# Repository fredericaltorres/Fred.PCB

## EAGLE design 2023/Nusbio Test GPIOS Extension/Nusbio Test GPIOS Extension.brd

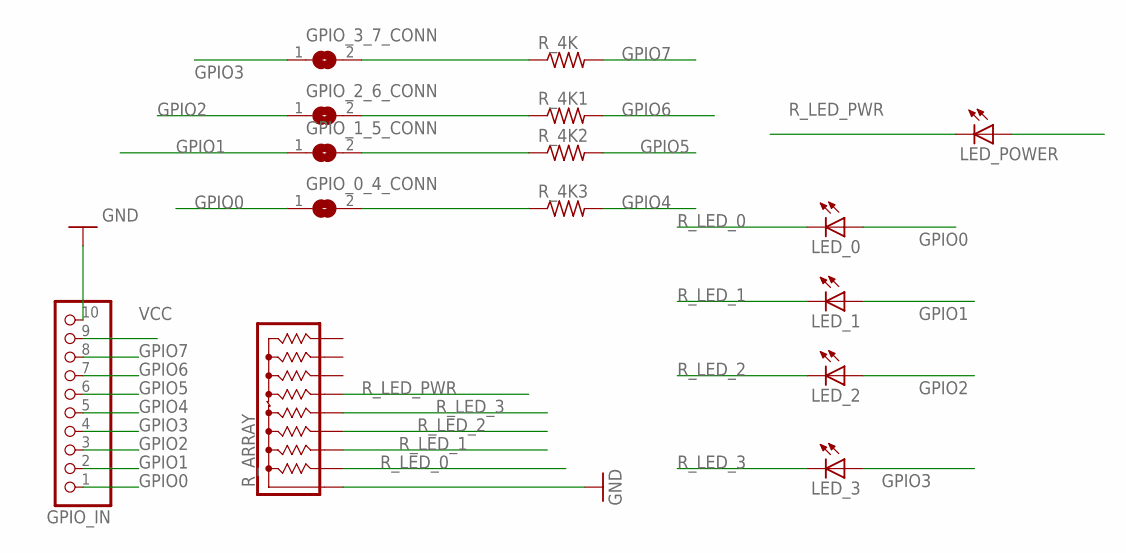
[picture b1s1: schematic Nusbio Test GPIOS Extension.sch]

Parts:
GPIO_0_4_CONN, GPIO_1_5_CONN, GPIO_2_6_CONN, GPIO_3_7_CONN: SOLDERJUMPERREFLOW; SOLDERJUMPER_REFLOW
GPIO_IN: PINHD-1X10; 1X10-BIG
LED_0, LED_1, LED_2, LED_3: LEDSMT1206; 1206
LED_POWER: LEDSMT1206; 1206
R_4K, R_4K1, R_4K2, R_4K3: R-US_R1206; R1206
R_ARRAY: 4609X; SIP9

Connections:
GND: GPIO_IN.10, R_ARRAY.1
GPIO0: GPIO_0_4_CONN.1, GPIO_IN.1, LED_0.A
GPIO1: GPIO_1_5_CONN.1, GPIO_IN.2, LED_1.A
GPIO2: GPIO_2_6_CONN.1, GPIO_IN.3, LED_2.A
GPIO3: GPIO_3_7_CONN.1, GPIO_IN.4, LED_3.A
GPIO4: GPIO_IN.5, R_4K3.2
GPIO5: GPIO_IN.6, R_4K2.2
GPIO6: GPIO_IN.7, R_4K1.2
GPIO7: GPIO_IN.8, R_4K.2; also elsewhere on the board
unnamed 9: GPIO_3_7_CONN.2, R_4K.1; also elsewhere on the board
unnamed: GPIO_2_6_CONN.2, R_4K1.1
unnamed: GPIO_1_5_CONN.2, R_4K2.1
unnamed: GPIO_0_4_CONN.2, R_4K3.1
R_LED_0: LED_0.C, R_ARRAY.2
R_LED_1: LED_1.C, R_ARRAY.3
R_LED_2: LED_2.C, R_ARRAY.4
R_LED_3: LED_3.C, R_ARRAY.5
R_LED_PWR: LED_POWER.C, R_ARRAY.6
VCC: GPIO_IN.9, LED_POWER.A

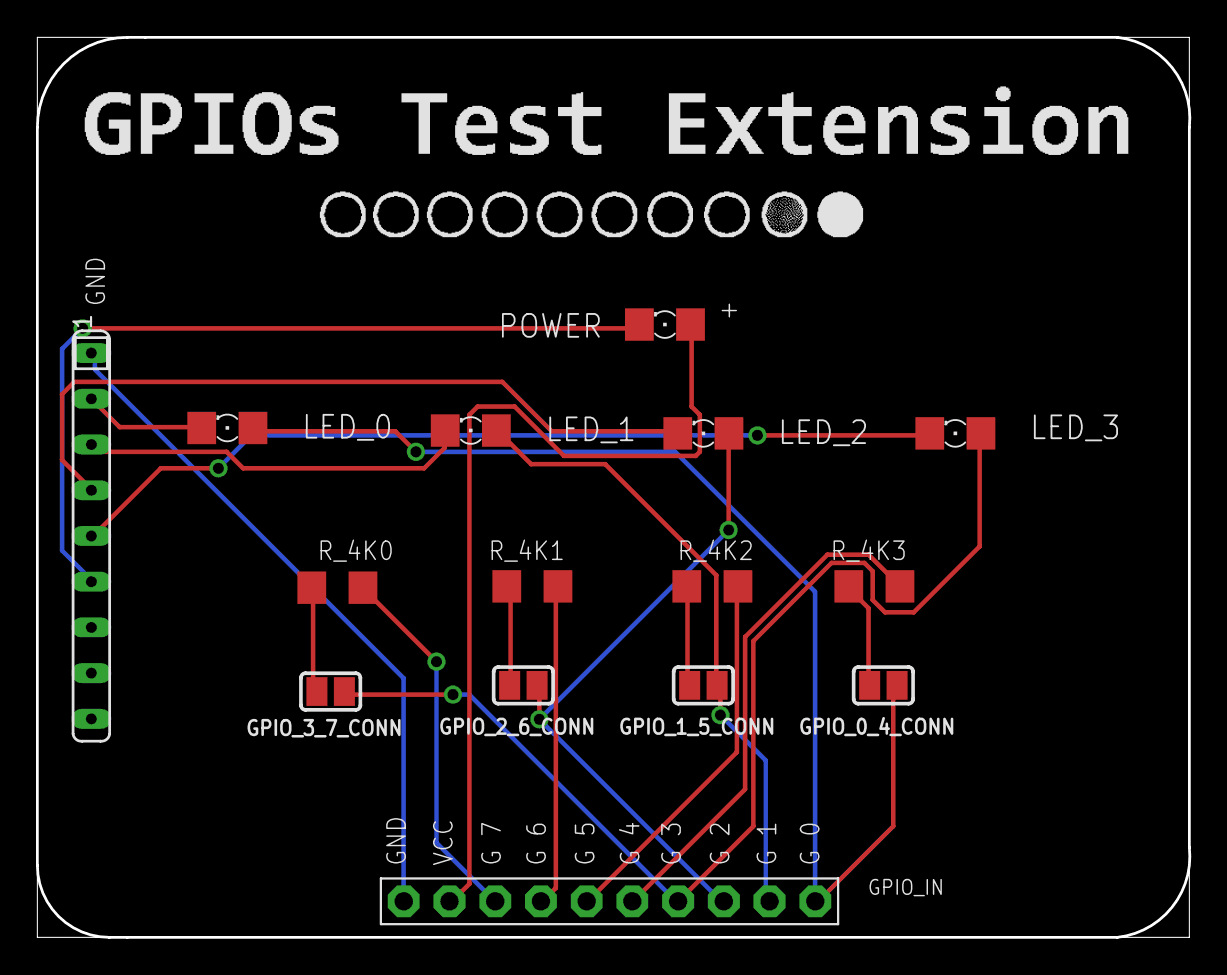
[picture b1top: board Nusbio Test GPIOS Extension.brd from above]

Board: 2 copper layers, 64.0 x 50.0 mm, 15 parts (0 on the bottom side), 19 nets.

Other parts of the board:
R_4K0: R1206

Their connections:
GPIO7: R_4K0.2; also elsewhere on the board
unnamed 9: R_4K0.1; also elsewhere on the board

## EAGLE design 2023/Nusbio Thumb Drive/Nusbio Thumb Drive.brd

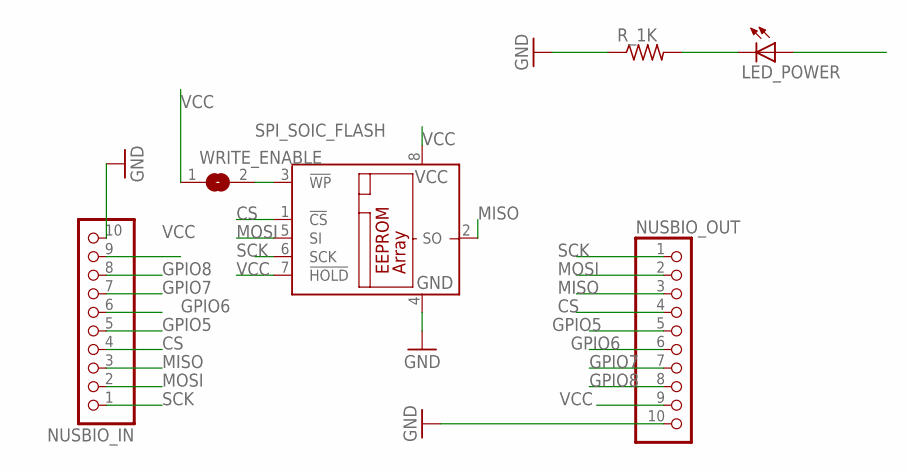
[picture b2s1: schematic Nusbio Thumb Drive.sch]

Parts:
LED_POWER: LEDSMT1206; 1206
NUSBIO_IN: PINHD-1X10; 1X10-BIG
NUSBIO_OUT: PINHD-1X10; 1X10-BIG
R_1K: R-US_R1206; R1206
SPI_SOIC_FLASH: 25AA080SN; SO-08
WRITE_ENABLE: SOLDERJUMPERREFLOW; SOLDERJUMPER_REFLOW

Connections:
CS: NUSBIO_IN.4, NUSBIO_OUT.4, SPI_SOIC_FLASH.1 (!CS)
GND: NUSBIO_IN.10, NUSBIO_OUT.10, R_1K.1, SPI_SOIC_FLASH.4 (GND)
GPIO5: NUSBIO_IN.5, NUSBIO_OUT.5
GPIO6: NUSBIO_IN.6, NUSBIO_OUT.6
GPIO7: NUSBIO_IN.7, NUSBIO_OUT.7
GPIO8: NUSBIO_IN.8, NUSBIO_OUT.8
MISO: NUSBIO_IN.3, NUSBIO_OUT.3, SPI_SOIC_FLASH.2 (SO)
MOSI: NUSBIO_IN.2, NUSBIO_OUT.2, SPI_SOIC_FLASH.5 (SI)
unnamed: SPI_SOIC_FLASH.3 (!WP), WRITE_ENABLE.2
unnamed: LED_POWER.C, R_1K.2
SCK: NUSBIO_IN.1, NUSBIO_OUT.1, SPI_SOIC_FLASH.6 (SCK)
VCC: LED_POWER.A, NUSBIO_IN.9, NUSBIO_OUT.9, SPI_SOIC_FLASH.7 (!HOLD), SPI_SOIC_FLASH.8 (VCC), WRITE_ENABLE.1

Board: 2 copper layers, 6 parts (0 on the bottom side), 12 nets, no tracks yet.

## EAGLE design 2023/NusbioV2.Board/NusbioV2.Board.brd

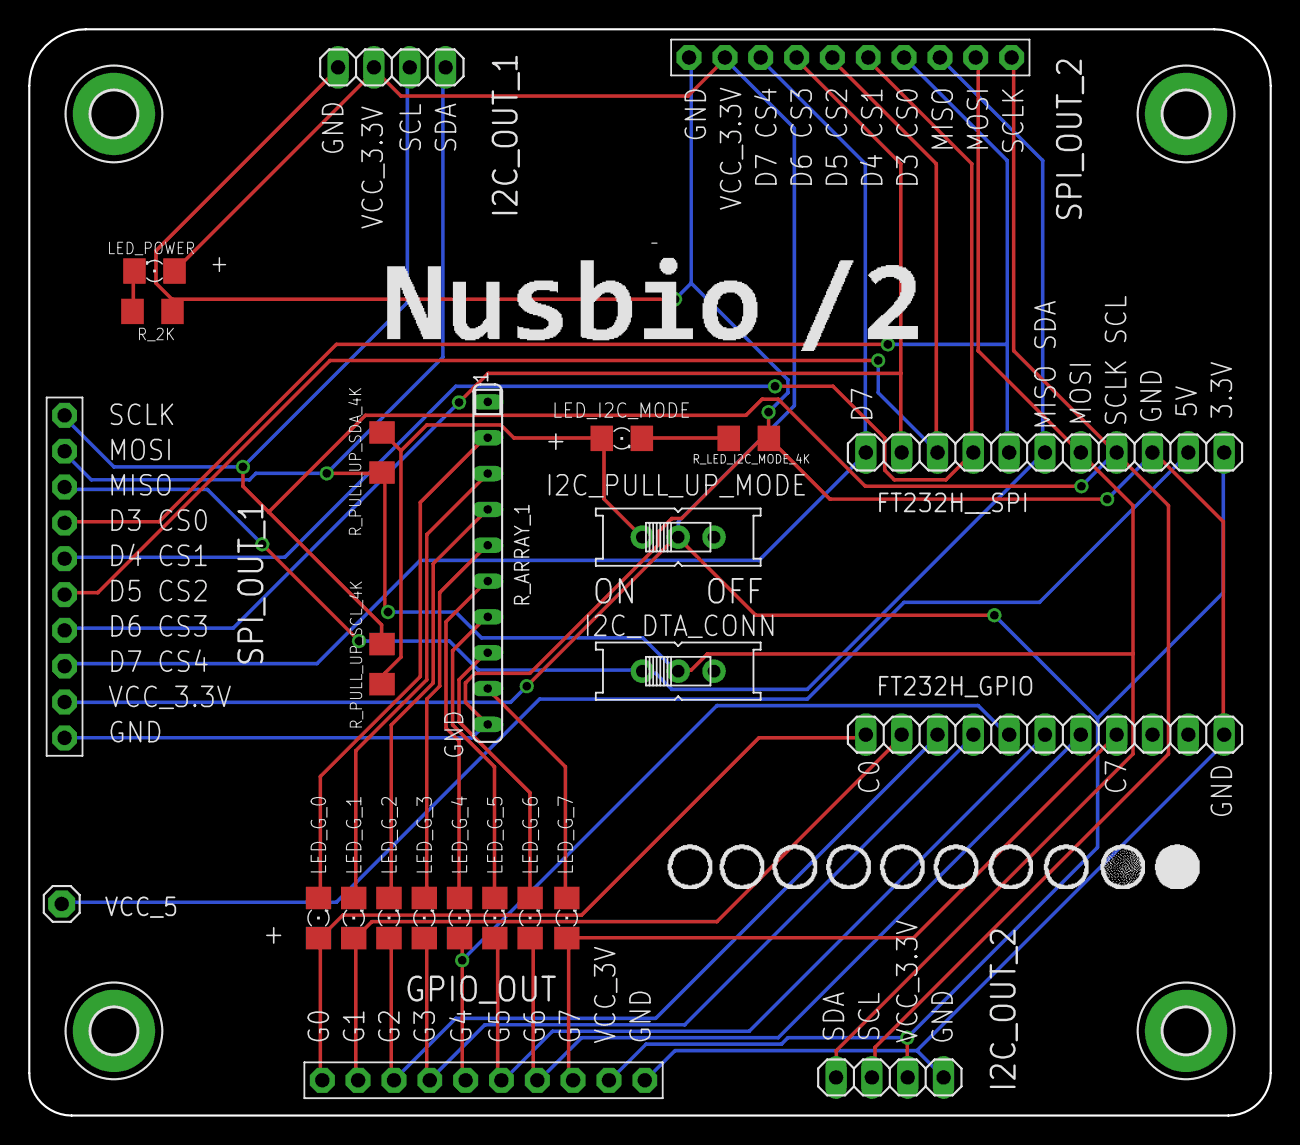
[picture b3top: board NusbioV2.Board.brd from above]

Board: 2 copper layers, 88.0 x 77.0 mm, 29 parts (0 on the bottom side), 30 nets.

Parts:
FT232H_GPIO, FT232H__SPI: 1X11
GPIO_OUT: PINHD-1X10; 1X10-BIG
H1, H2, H3, H4: MOUNT-PAD-ROUND3.3; 3,3-PAD
I2C_DTA_CONN, I2C_PULL_UP_MODE: EG1218
I2C_OUT_1, I2C_OUT_2: 1X04
LED_G_0, LED_G_1, LED_G_2, LED_G_3, LED_G_4, LED_G_5, LED_G_6, LED_G_7: 1206
LED_I2C_MODE: 1206
LED_POWER: 1206
R_2K: R1206
R_ARRAY_1: SIP10
R_LED_I2C_MODE_4K: R1206
R_PULL_UP_SCL_4K: R1206
R_PULL_UP_SDA_4K: R1206
SPI_OUT_1, SPI_OUT_2: PINHD-1X10; 1X10-BIG
VCC_5: 1X01

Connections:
C0: FT232H_GPIO.1, GPIO_OUT.10, LED_G_0.A
C1: FT232H_GPIO.2, GPIO_OUT.9, LED_G_1.A
C2: FT232H_GPIO.3, GPIO_OUT.8, LED_G_2.A
C3: FT232H_GPIO.4, GPIO_OUT.7, LED_G_3.A
C4: FT232H_GPIO.5, GPIO_OUT.6, LED_G_4.A
C5: FT232H_GPIO.6, GPIO_OUT.5, LED_G_5.A
C6: FT232H_GPIO.7, GPIO_OUT.4, LED_G_6.A
C7: FT232H_GPIO.8, GPIO_OUT.3, LED_G_7.A
D0_SCLK: FT232H__SPI.8, I2C_OUT_1.2, I2C_OUT_2.2, R_PULL_UP_SCL_4K.1, SPI_OUT_1.10, SPI_OUT_2.10
D1_MOSI: FT232H__SPI.7, I2C_DTA_CONN.P, I2C_OUT_1.1, I2C_OUT_2.1, R_PULL_UP_SDA_4K.1, SPI_OUT_1.9, SPI_OUT_2.9
D2_MISO: FT232H__SPI.6, I2C_DTA_CONN.O, SPI_OUT_1.8, SPI_OUT_2.8
D3_CS0: FT232H__SPI.5, SPI_OUT_1.7, SPI_OUT_2.7
D4_CS1: FT232H__SPI.4, SPI_OUT_1.6, SPI_OUT_2.6
D5_CS2: FT232H__SPI.3, SPI_OUT_1.5, SPI_OUT_2.5
D6_CS3: FT232H__SPI.2, SPI_OUT_1.4, SPI_OUT_2.4
D7_CS4: FT232H__SPI.1, SPI_OUT_1.3, SPI_OUT_2.3
GND: FT232H_GPIO.11, FT232H__SPI.9, GPIO_OUT.1, I2C_OUT_1.4, I2C_OUT_2.4, R_2K.1, R_ARRAY_1.10, R_LED_I2C_MODE_4K.1, SPI_OUT_1.1, SPI_OUT_2.1
unnamed: LED_POWER.C, R_2K.2
unnamed: I2C_PULL_UP_MODE.O, LED_I2C_MODE.A, R_PULL_UP_SCL_4K.2, R_PULL_UP_SDA_4K.2
unnamed: LED_I2C_MODE.C, R_LED_I2C_MODE_4K.2
R_G_0: LED_G_0.C, R_ARRAY_1.2
R_G_1: LED_G_1.C, R_ARRAY_1.3
R_G_2: LED_G_2.C, R_ARRAY_1.4
R_G_3: LED_G_3.C, R_ARRAY_1.5
R_G_4: LED_G_4.C, R_ARRAY_1.6
R_G_5: LED_G_5.C, R_ARRAY_1.7
R_G_6: LED_G_6.C, R_ARRAY_1.8
R_G_7: LED_G_7.C, R_ARRAY_1.9
VCC_5: FT232H__SPI.10, VCC_5.1
VCC_33: FT232H__SPI.11, GPIO_OUT.2, I2C_OUT_1.3, I2C_OUT_2.3, I2C_PULL_UP_MODE.P, LED_POWER.A, SPI_OUT_1.2, SPI_OUT_2.2

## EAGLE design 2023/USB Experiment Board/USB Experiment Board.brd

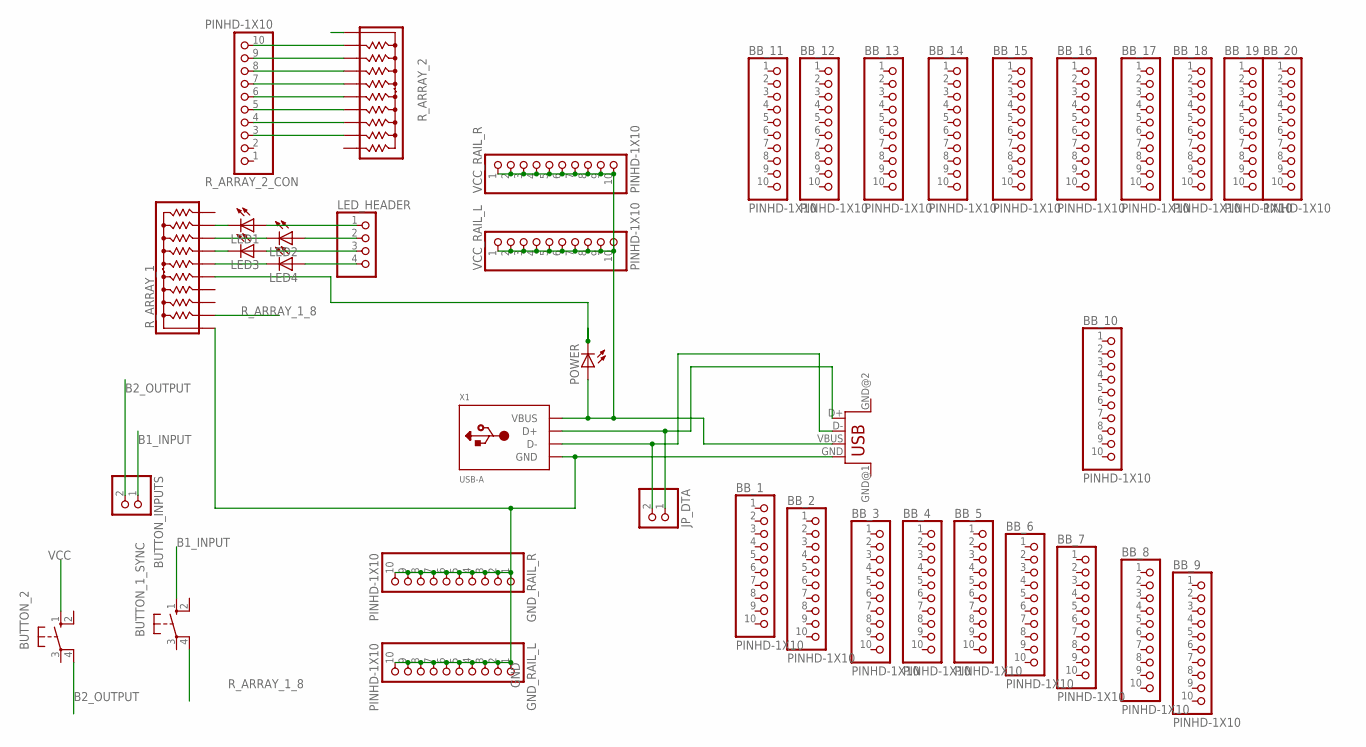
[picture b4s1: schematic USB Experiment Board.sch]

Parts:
BB_1, BB_2, BB_3, BB_4, BB_5, BB_6, BB_7, BB_8, BB_9, BB_10, BB_11, BB_12, BB_13, BB_14, BB_15, BB_16, BB_17, BB_18, BB_19, BB_20: PINHD-1X10; 1X10-BIG
BUTTON_1_SYNC, BUTTON_2: 10-XX; B3F-10XX
BUTTON_INPUTS: PINHD-1X2; 1X02
GND_RAIL_L: PINHD-1X10; 1X10-BIG
GND_RAIL_R: PINHD-1X10; 1X10-BIG
JP_DTA: PINHD-1X2; 1X02
LED1, LED2, LED3, LED4: LEDSMT1206; 1206
LED_HEADER: PINHD-1X4; 1X04
POWER: LEDSMT1206; 1206
R_ARRAY_1, R_ARRAY_2: 4610X; SIP10
R_ARRAY_2_CON: PINHD-1X10; 1X10-BIG
U$1: USB; USB-FEMALE-A-PTH
VCC_RAIL_L: PINHD-1X10; 1X10-BIG
VCC_RAIL_R: PINHD-1X10; 1X10-BIG
X1: USB-A; MOLEX_480371000

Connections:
B1_INPUT: BUTTON_1_SYNC.1 (S), BUTTON_INPUTS.1
B2_OUTPUT: BUTTON_2.4 (P1), BUTTON_INPUTS.2
GND: GND_RAIL_L.1, GND_RAIL_L.2, GND_RAIL_L.3, GND_RAIL_L.4, GND_RAIL_L.5, GND_RAIL_L.6, GND_RAIL_L.7, GND_RAIL_L.8, GND_RAIL_L.9, GND_RAIL_L.10, GND_RAIL_R.1, GND_RAIL_R.2, GND_RAIL_R.3, GND_RAIL_R.4, GND_RAIL_R.5, GND_RAIL_R.6, GND_RAIL_R.7, GND_RAIL_R.8, GND_RAIL_R.9, GND_RAIL_R.10, R_ARRAY_1.1, R_ARRAY_2.1, U$1.GND, X1.4 (GND)
unnamed: R_ARRAY_2.2, R_ARRAY_2_CON.10
unnamed: LED1.C, R_ARRAY_1.9
unnamed: JP_DTA.1, U$1.D+, X1.3 (D+)
unnamed: JP_DTA.2, U$1.D-, X1.2 (D-)
unnamed: LED2.C, R_ARRAY_1.8
unnamed: LED3.C, R_ARRAY_1.7
unnamed: LED4.C, R_ARRAY_1.6
unnamed: LED1.A, LED_HEADER.1
unnamed: LED2.A, LED_HEADER.2
unnamed: LED3.A, LED_HEADER.3
unnamed: LED4.A, LED_HEADER.4
unnamed: R_ARRAY_2.3, R_ARRAY_2_CON.9
unnamed: POWER.C, R_ARRAY_1.5
unnamed: R_ARRAY_2.4, R_ARRAY_2_CON.8
unnamed: R_ARRAY_2.5, R_ARRAY_2_CON.7
unnamed: R_ARRAY_2.6, R_ARRAY_2_CON.6
unnamed: R_ARRAY_2.7, R_ARRAY_2_CON.5
unnamed: R_ARRAY_2.8, R_ARRAY_2_CON.4
unnamed: R_ARRAY_2.9, R_ARRAY_2_CON.3
R_ARRAY_1_8: BUTTON_1_SYNC.4 (P1), R_ARRAY_1.2
VCC: BUTTON_2.1 (S), POWER.A, U$1.VBUS, VCC_RAIL_L.1, VCC_RAIL_L.2, VCC_RAIL_L.3, VCC_RAIL_L.4, VCC_RAIL_L.5, VCC_RAIL_L.6, VCC_RAIL_L.7, VCC_RAIL_L.8, VCC_RAIL_L.9, VCC_RAIL_L.10, VCC_RAIL_R.1, VCC_RAIL_R.2, VCC_RAIL_R.3, VCC_RAIL_R.4, VCC_RAIL_R.5, VCC_RAIL_R.6, VCC_RAIL_R.7, VCC_RAIL_R.8, VCC_RAIL_R.9, VCC_RAIL_R.10, X1.1 (VBUS)

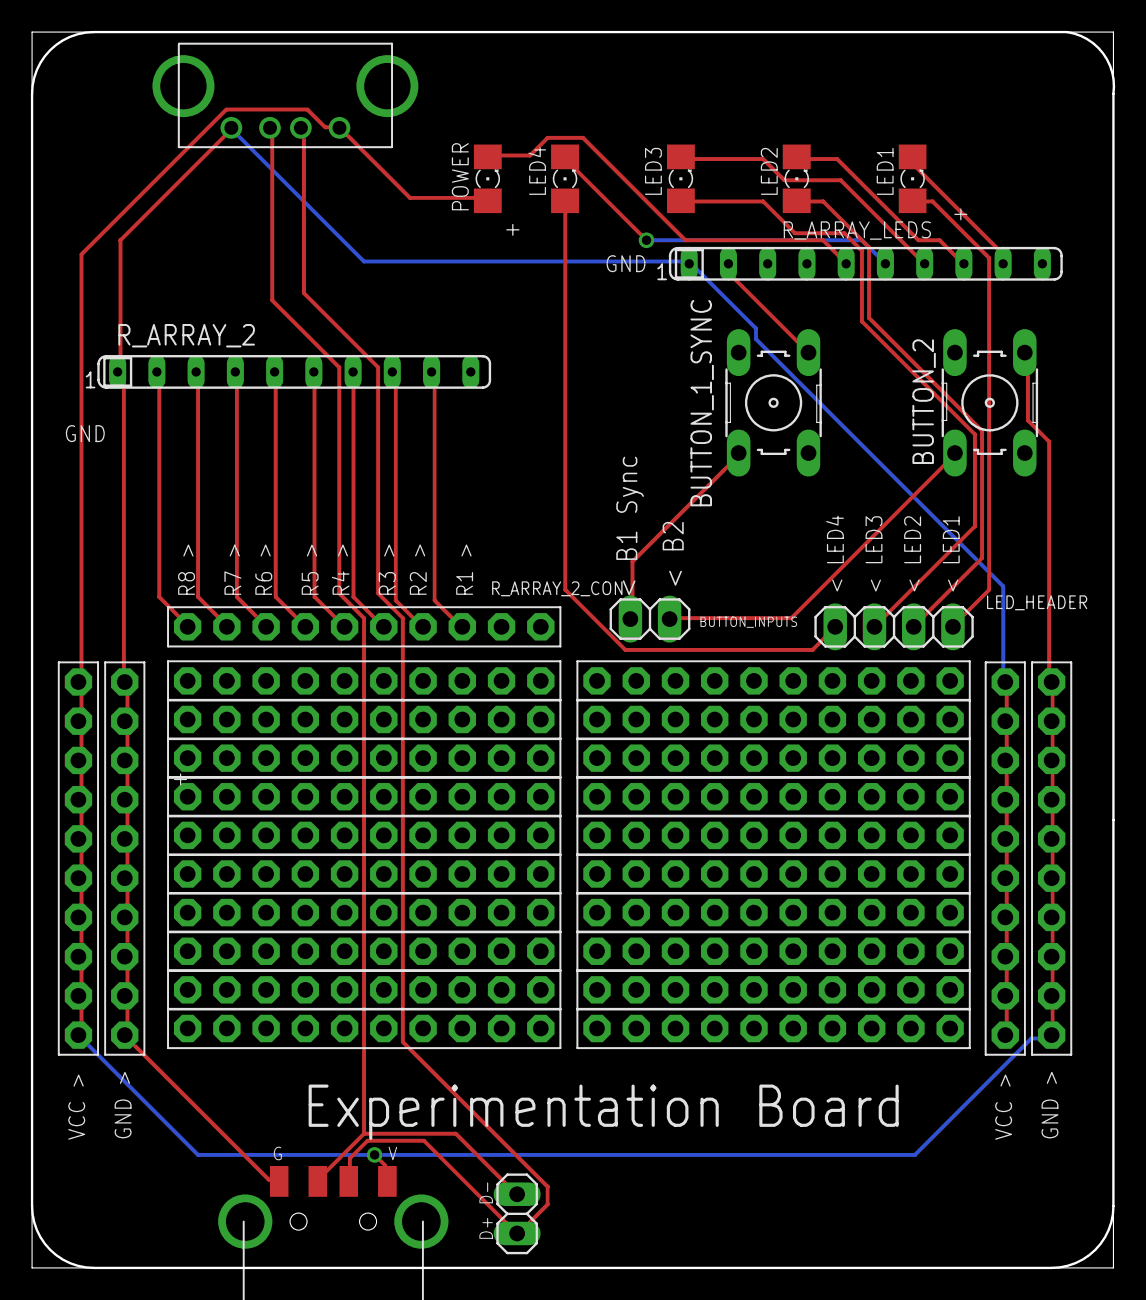
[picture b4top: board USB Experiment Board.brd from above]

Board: 2 copper layers, 70.0 x 80.0 mm, 39 parts (0 on the bottom side), 24 nets.

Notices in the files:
parts and their libraries:
microbuilder: This work is placed in the public domain, and may be freely used for commercial and non-commercial work with the following conditions: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
